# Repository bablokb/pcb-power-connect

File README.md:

pcb-power-connect
=================

In this repository you will find a small pcb useful if you
want to feed power to your Pi using GPIO pins 2 and 4 (e.g.
because the pi is within a housing and there is no space for
a connection to the usb-power plug of the pi).

The pcb supports some additional features

  - connect an external high->low signal (e.g. button)
    to GPIO3 (acts as on/off-switch, see below)
  - connect an external low->high signal to GPIO3 via an
    inverter (74HC05)
  - connect a LED
  - connect an IR (or something else)
  - connect an UART

 Pinout
 ------
 
  -  1: 3V3
  -  2: 5V
  -  3: GPIO2: nc
  -  4: 5V
  -  5: GPIO3: on/off
  -  6: GND
  -  7: GPIO4: IR
  -  8: GPIO14: TX
  -  9: GND
  - 10: GPIO15: RX
  - 11: GPIO17: LED
  - 12: GPIO18: nc

Configuration
-------------

Use the following configuration in `/boot/config.txt`:

    # configure GPIO3 as shutdown-button
    dtoverlay=gpio-shutdown
    
    # configure GPIO4 for IR
    dtoverlay=gpio-ir,gpio_pin=4

    # use external heartbeat-LED
    dtparam=act_led_trigger=heartbeat
    dtoverlay=act-led,gpio=17

License
-------

Shield: [![CC BY-SA 4.0][cc-by-sa-shield]][cc-by-sa]

This work is licensed under a
[Creative Commons Attribution-ShareAlike 4.0 International
License][cc-by-sa].

[![CC BY-SA 4.0][cc-by-sa-image]][cc-by-sa]

[cc-by-sa]: http://creativecommons.org/licenses/by-sa/4.0/
[cc-by-sa-image]: https://licensebuttons.net/l/by-sa/4.0/88x31.png
[cc-by-sa-shield]:
https://img.shields.io/badge/License-CC%20BY--SA%204.0-lightgrey.svg

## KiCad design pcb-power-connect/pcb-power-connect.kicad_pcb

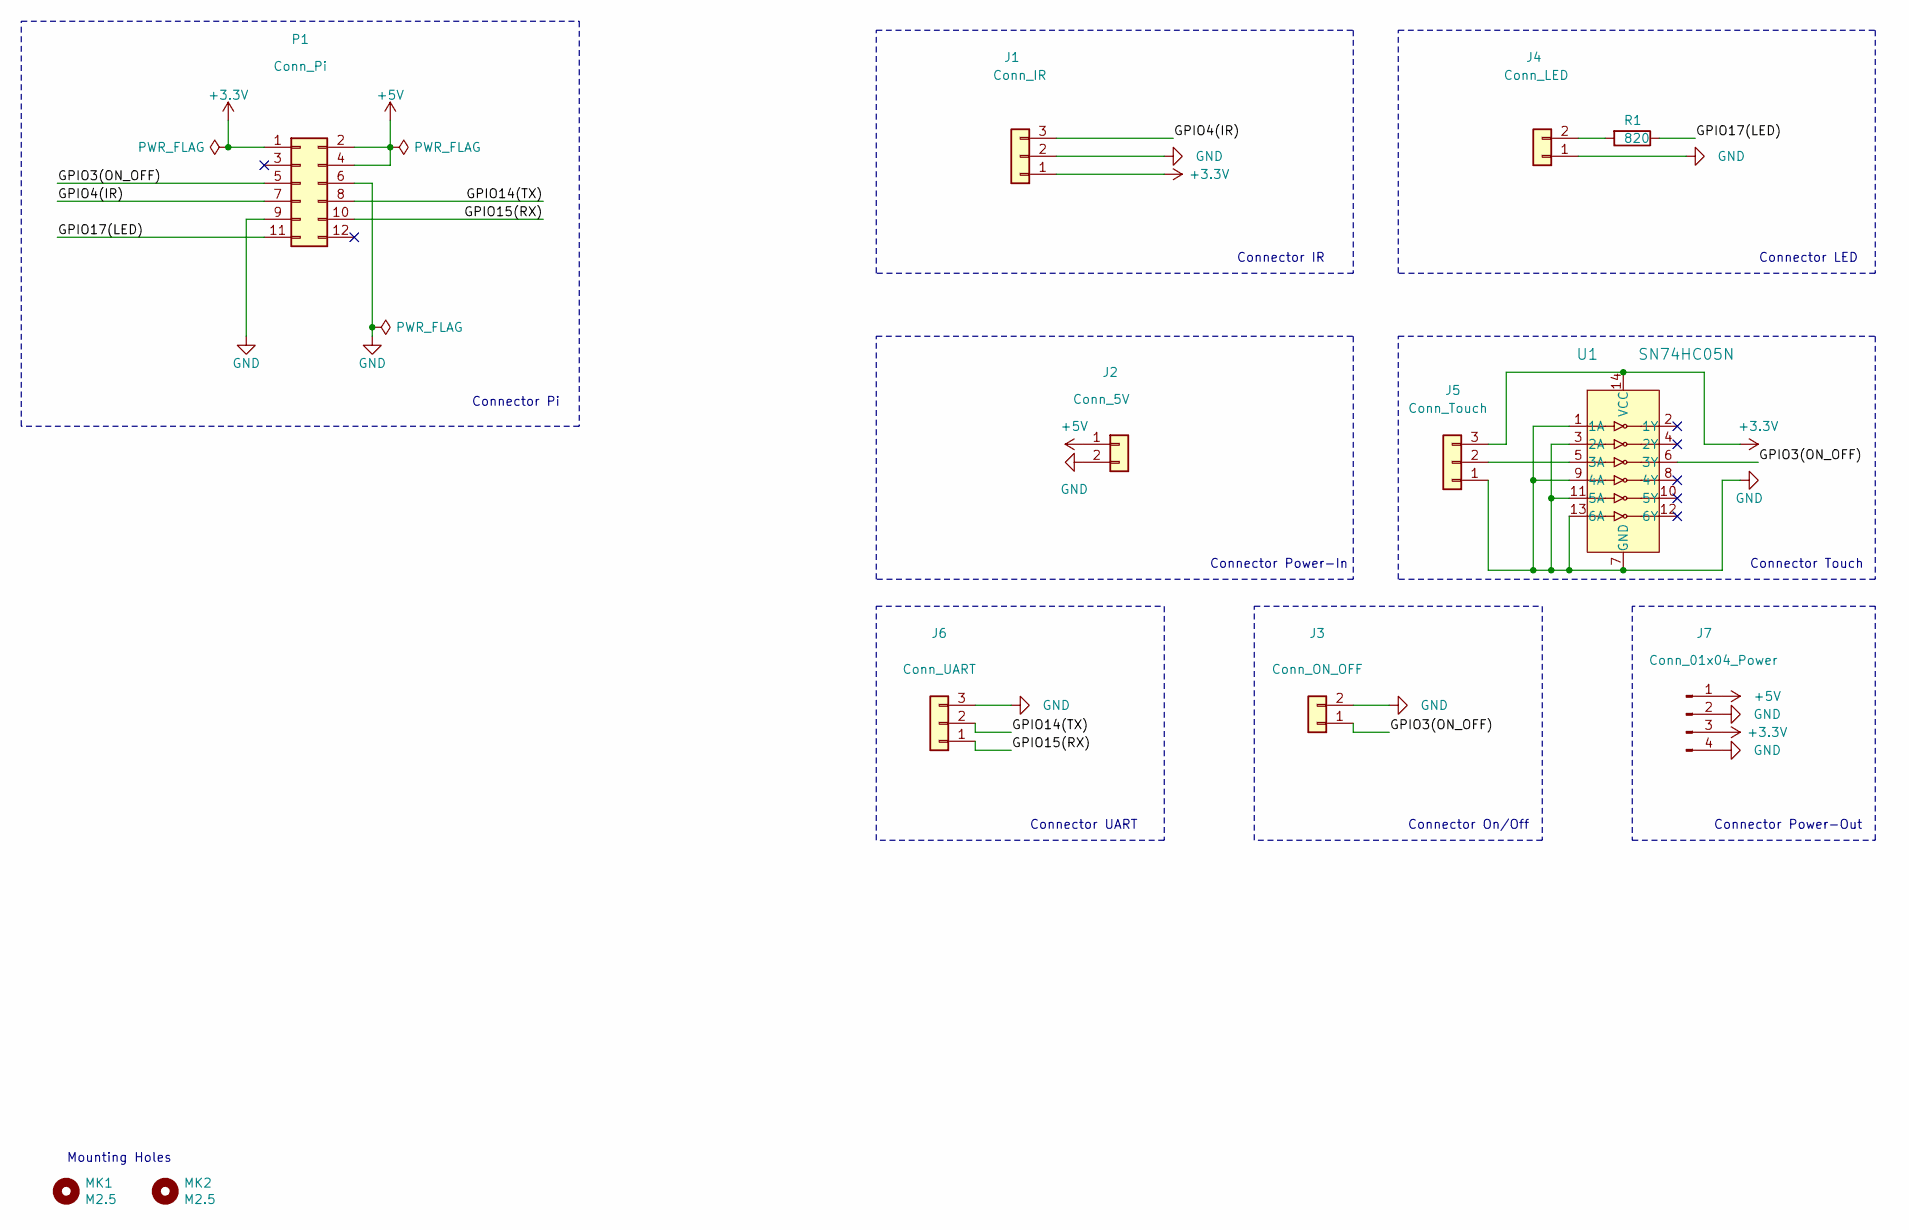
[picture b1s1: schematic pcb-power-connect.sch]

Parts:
J1: Conn_IR; PinHeader_1x03_P2.54mm_Vertical
J2: Conn_5V; TerminalBlock_MetzConnect_Type182_PT11302HBBN_1x02_P3.50mm_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
J3: Conn_ON_OFF; PinHeader_1x02_P2.54mm_Vertical
J4: Conn_LED; PinHeader_1x02_P2.54mm_Vertical
J5: Conn_Touch; PinHeader_1x03_P2.54mm_Vertical
J6: Conn_UART; PinHeader_1x03_P2.54mm_Vertical
J7: Conn_01x04_Power; PinHeader_1x04_P2.54mm_Vertical
MK1, MK2: M2.5; MountingHole_2.7mm_M2.5
P1: Conn_Pi; PinSocket_2x06_P2.54mm_Vertical
R1: 820; R_1206_3216Metric_Pad1.30x1.75mm_HandSolder; LCSC C17837
U1: SN74HC05N; SO-14_3.9x8.65mm_P1.27mm_HandSolder

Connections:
+3V3: J1.1, J5.3, J7.3, P1.1, U1.14 (VCC)
+5V: J2.1, J7.1, P1.2, P1.4
/GPIO3(ON_OFF): J3.1, P1.5, U1.6 (3Y)
/GPIO4(IR): J1.3, P1.7
/GPIO14(TX): J6.2, P1.8
/GPIO15(RX): J6.1, P1.10
/GPIO17(LED): P1.11, R1.1
GND: J1.2, J2.2, J3.2, J4.1, J5.1, J6.3, J7.2, J7.4, P1.6, P1.9, U1.1 (1A), U1.3 (2A), U1.7 (GND), U1.9 (4A), U1.11 (5A), U1.13 (6A)
unnamed: J4.2, R1.2
unnamed: J5.2, U1.5 (3A)

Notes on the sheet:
Mounting Holes
Connector Pi
Connector LED
Connector On/Off
Connector IR
Connector Touch
Connector Power-In
Connector UART
Connector Power-Out

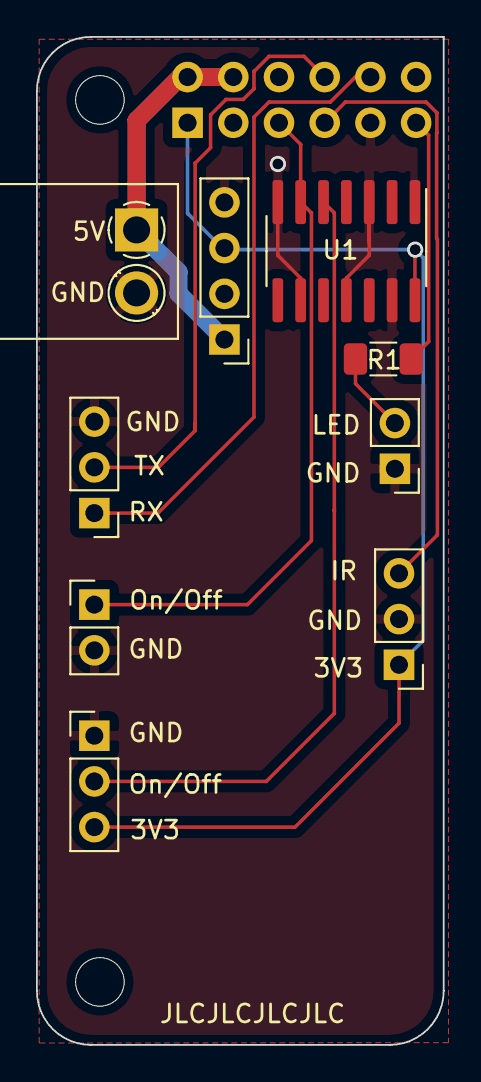
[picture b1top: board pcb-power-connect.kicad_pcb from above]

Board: 2 copper layers, 22.6 x 56.0 mm, 12 parts (1 on the bottom side), 10 nets.

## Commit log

2021-07-17 added content
2021-07-17 link to image of pcb
2021-07-17 added LED-configuration
2021-10-30 added section about license
